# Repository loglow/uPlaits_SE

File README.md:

# µPlaits SE (uPlaits, microPlaits) Eurorack [Rev C]

## 8HP Eurorack module | Macro-oscillator

[µPlaits SE](http://uplaits-se.com) is a voltage-controlled sound source offering direct access to a large palette of easily tweakable raw sonic material generated by models spanning a wide range of synthesis techniques.

This re-engineered Eurorack module miniaturizes and redesigns the original [Mutable Instruments Plaits](https://mutable-instruments.net/modules/plaits/), reducing its size from 12HP to 8HP and reworking its front panel layout.

Fully compatible with upstream Plaits firmware. Includes power cable, mounting hardware, and a one-year warranty. Designed and built with care by [Tall Dog Electronics](http://tall-dog.com) in Western Massachusetts. Licensed [CC BY-SA 4.0](https://creativecommons.org/licenses/by-sa/4.0/) open source hardware.

- **Height:** 3U (128.5 mm)
- **Width:** 8HP (40.3 mm)
- **Depth:** 43 mm (with power)
- **+12V:** 50 mA (average)
- **-12V:** 5 mA (average)

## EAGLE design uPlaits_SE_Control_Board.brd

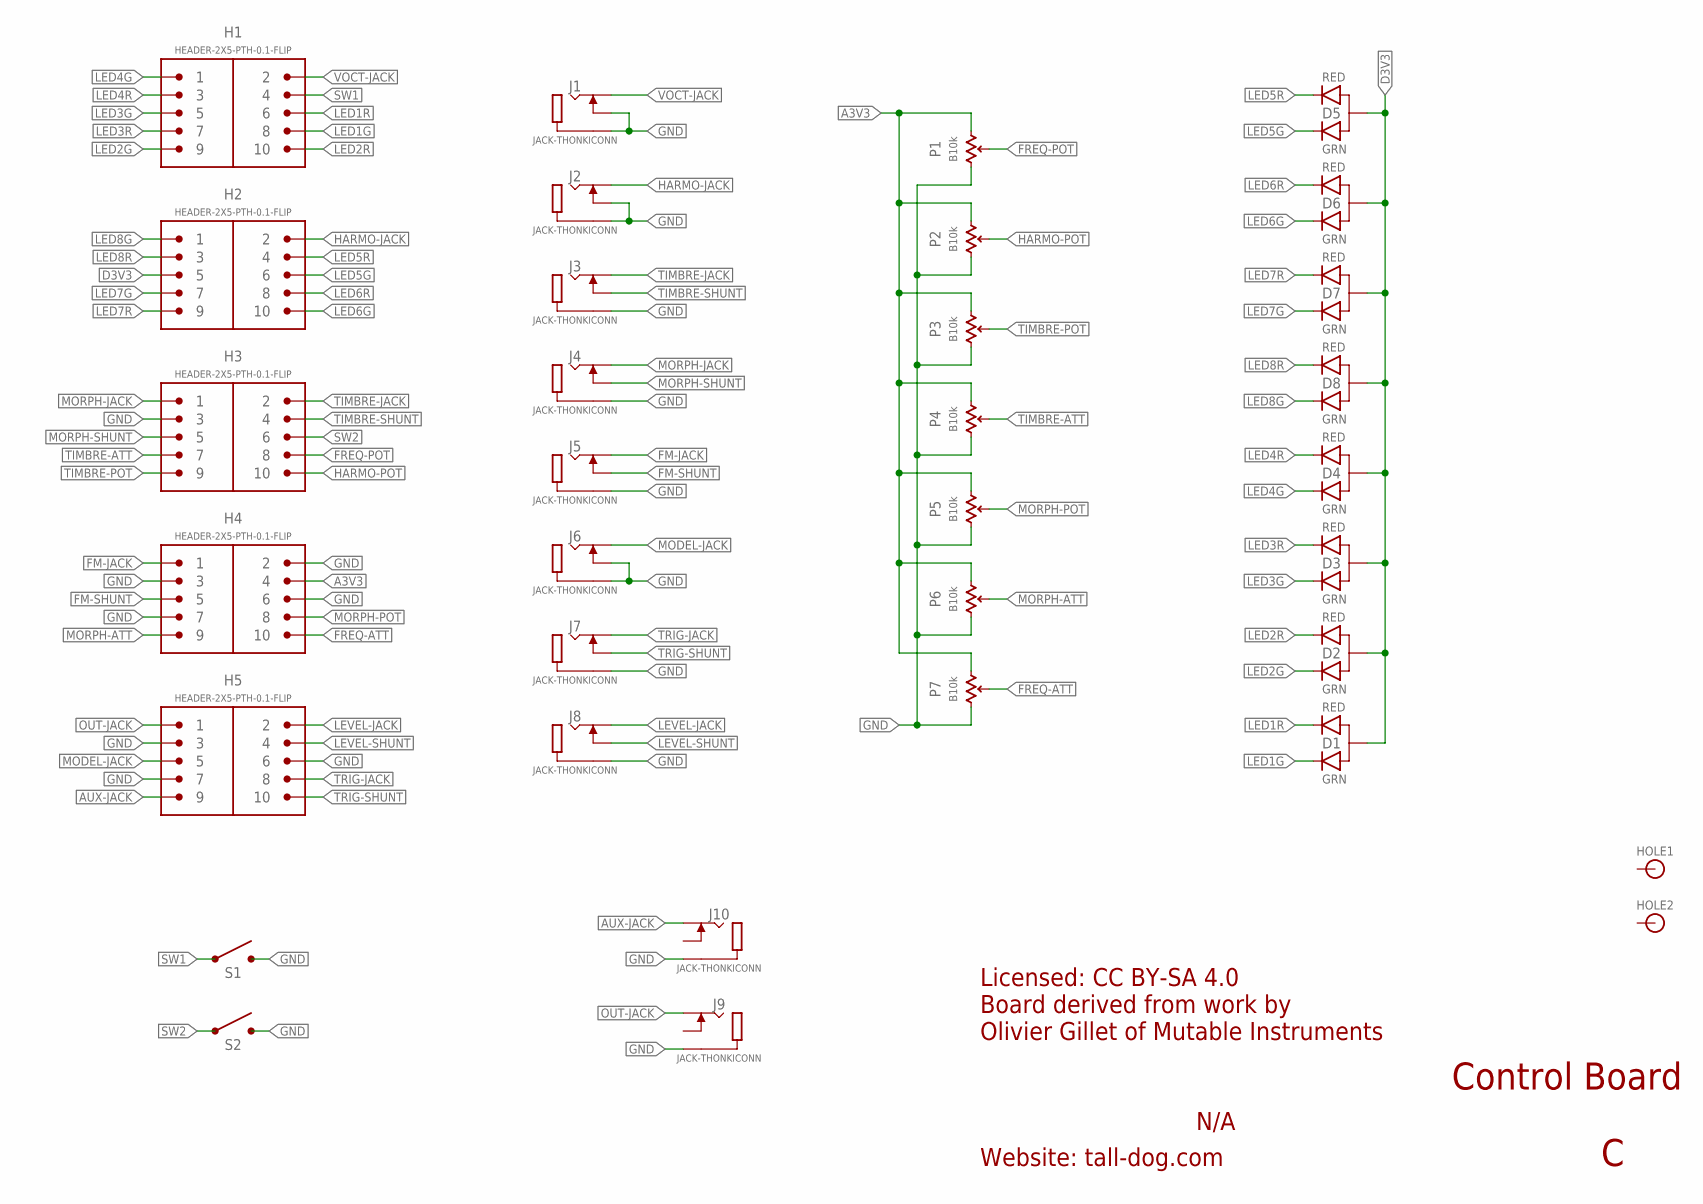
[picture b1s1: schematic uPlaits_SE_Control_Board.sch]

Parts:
D1, D2, D3, D4, D5, D6, D7, D8: LED-DUAL-PTH; LED-T1-3
H1, H2, H3, H4, H5: HEADER-2X5-PTH-0.1-FLIP; PTH-0.1-2X5-FLIP
HOLE1, HOLE2: HOLE; HOLE-M2.5
J1, J2, J3, J4, J5, J6, J7, J8, J9, J10: JACK-THONKICONN; THONKICONN
P1, P2, P3, P4, P5, P6, P7: B10k; POT-SONG-9MM
S1, S2: SPST-PTH; TL1105

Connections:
A3V3: H4.4, P1.P$1 (E), P2.P$1 (E), P3.P$1 (E), P4.P$1 (E), P5.P$1 (E), P6.P$1 (E), P7.P$1 (E)
AUX-JACK: H5.9, J10.P3 (3)
D3V3: D1.2 (A), D2.2 (A), D3.2 (A), D4.2 (A), D5.2 (A), D6.2 (A), D7.2 (A), D8.2 (A), H2.5
FM-JACK: H4.1, J5.P3 (3)
FM-SHUNT: H4.5, J5.P2 (2)
FREQ-ATT: H4.10, P7.P$2 (S)
FREQ-POT: H3.8, P1.P$2 (S)
GND: H3.3, H4.2, H4.3, H4.6, H4.7, H5.3, H5.6, H5.7, J1.P1 (1), J1.P2 (2), J2.P1 (1), J2.P2 (2), J3.P1 (1), J4.P1 (1), J5.P1 (1), J6.P1 (1), J6.P2 (2), J7.P1 (1), J8.P1 (1), J9.P1 (1), J10.P1 (1), P1.P$3 (A), P2.P$3 (A), P3.P$3 (A), P4.P$3 (A), P5.P$3 (A), P6.P$3 (A), P7.P$3 (A), S1.3 (2), S1.4 (2), S2.3 (2), S2.4 (2)
HARMO-JACK: H2.2, J2.P3 (3)
HARMO-POT: H3.10, P2.P$2 (S)
LED1G: D1.3 (GRN), H1.8
LED1R: D1.1 (RED), H1.6
LED2G: D2.3 (GRN), H1.9
LED2R: D2.1 (RED), H1.10
LED3G: D3.3 (GRN), H1.5
LED3R: D3.1 (RED), H1.7
LED4G: D4.3 (GRN), H1.1
LED4R: D4.1 (RED), H1.3
LED5G: D5.3 (GRN), H2.6
LED5R: D5.1 (RED), H2.4
LED6G: D6.3 (GRN), H2.10
LED6R: D6.1 (RED), H2.8
LED7G: D7.3 (GRN), H2.7
LED7R: D7.1 (RED), H2.9
LED8G: D8.3 (GRN), H2.1
LED8R: D8.1 (RED), H2.3
LEVEL-JACK: H5.2, J8.P3 (3)
LEVEL-SHUNT: H5.4, J8.P2 (2)
MODEL-JACK: H5.5, J6.P3 (3)
MORPH-ATT: H4.9, P6.P$2 (S)
MORPH-JACK: H3.1, J4.P3 (3)
MORPH-POT: H4.8, P5.P$2 (S)
MORPH-SHUNT: H3.5, J4.P2 (2)
OUT-JACK: H5.1, J9.P3 (3)
SW1: H1.4, S1.1, S1.2 (1)
SW2: H3.6, S2.1, S2.2 (1)
TIMBRE-ATT: H3.7, P4.P$2 (S)
TIMBRE-JACK: H3.2, J3.P3 (3)
TIMBRE-POT: H3.9, P3.P$2 (S)
TIMBRE-SHUNT: H3.4, J3.P2 (2)
TRIG-JACK: H5.8, J7.P3 (3)
TRIG-SHUNT: H5.10, J7.P2 (2)
VOCT-JACK: H1.2, J1.P3 (3)

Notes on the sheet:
Licensed: CC BY-SA 4.0 Board derived from work by Olivier Gillet of Mutable Instruments
Website: tall-dog.com
N/A
Control Board

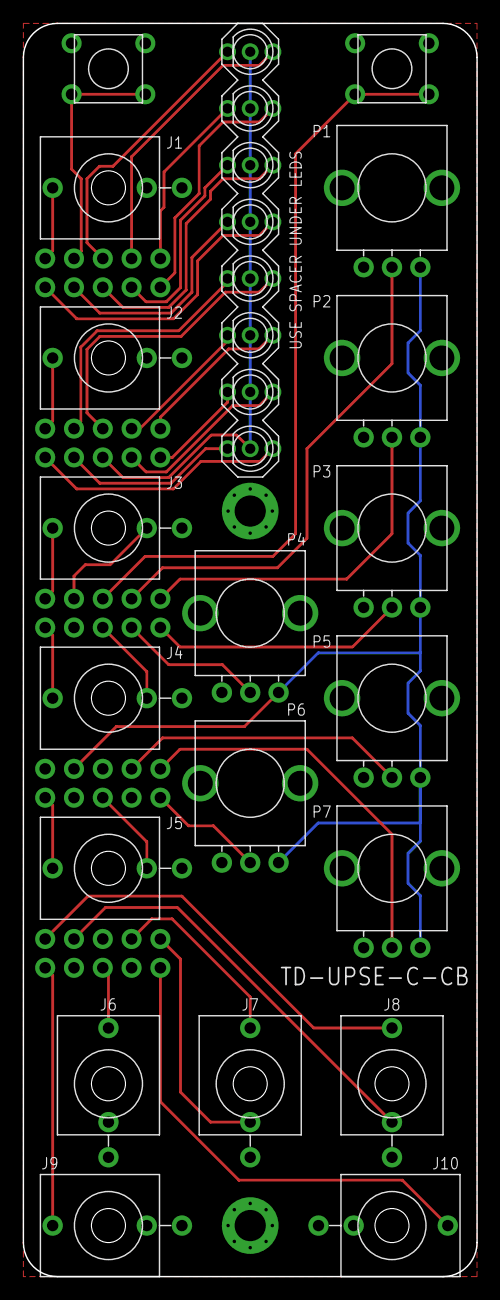
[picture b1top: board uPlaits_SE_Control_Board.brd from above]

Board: 2 copper layers, 40.0 x 110.5 mm, 35 parts (0 on the bottom side), 43 nets.

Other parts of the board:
U$1: LED-SPACER

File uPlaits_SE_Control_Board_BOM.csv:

Ref,Qty,Desc,Mfg,MPN
D1 D2 D3 D4 D5 D6 D7 D8,8,LED GREEN/RED DIFF T-3MM TRI T/H,Lumex Opto/Components Inc.,SSL-LX3059IGW-CA
H1 H2 H3 H4 H5,5,CONN HEADER VERT 10POS 2.54MM,Amphenol ICC (FCI),67997-210HLF
J1 J2 J3 J4 J5 J6 J7 J8 J9 J10,10,3.5MM JACK VERTICAL PCB MOUNT,Wenzhou QingPu,WQP-WQP518MA
P1 P2 P3 P5,4,POT 9MM LINEAR B10K WHITE LINE,Song Huei,"R0904N-B10K,L-25KQ/LWS"
P4 P6 P7,3,POT 9MM LINEAR B10K WHITE LINE CENTER DETENT,Song Huei,"R0904N-B10K,L-25KQ/LWS/CC"
S1 S2,2,SWITCH TACTILE SPST-NO 0.05A 12V,E-Switch,TL1105DF160Q

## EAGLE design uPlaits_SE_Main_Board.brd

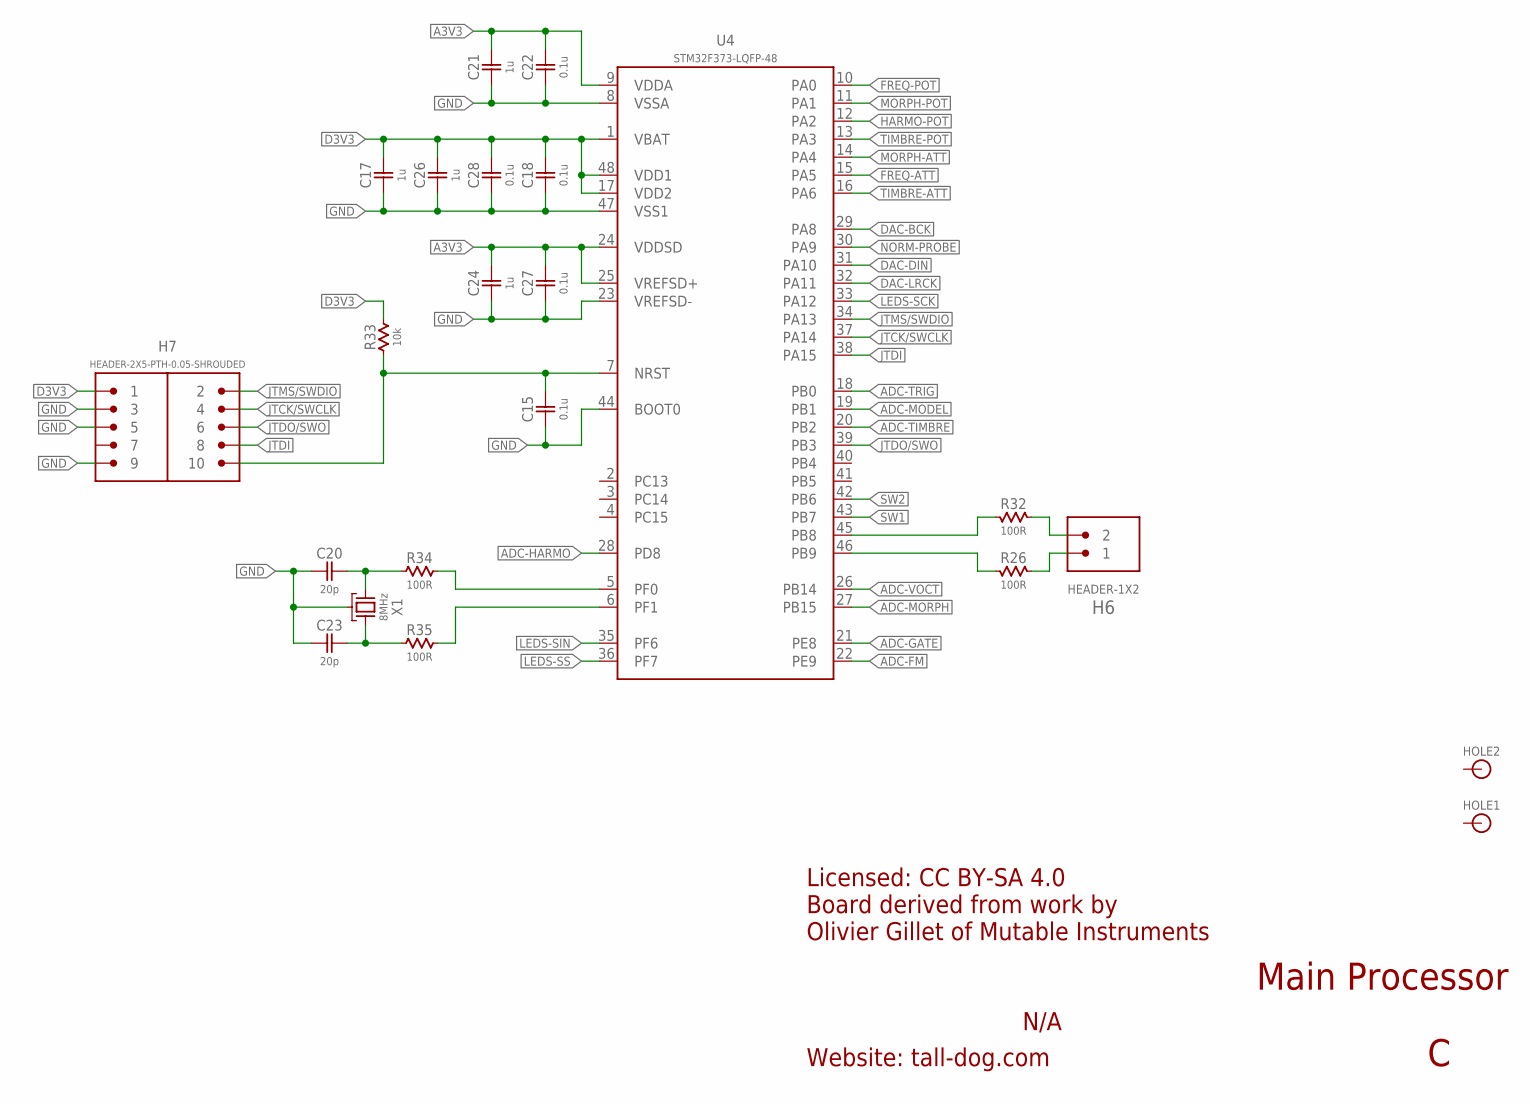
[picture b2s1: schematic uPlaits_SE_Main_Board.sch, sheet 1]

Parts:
C15, C18, C22, C27, C28: 0.1u; 0603-NP
C17, C21, C24, C26: 1u; 0603-NP
C20, C23: 20p; 0603-NP
H6: HEADER-1X2; PTH-0.1-1X2
H7: HEADER-2X5-PTH-0.05-SHROUDED; PTH-0.05-2X5-SHROUDED
HOLE1, HOLE2: HOLE; HOLE-M2.5
R26, R32, R34, R35: 100R; 0603-NP
R33: 10k; 0603-NP
U4: STM32F373-LQFP-48; LQFP-48
X1: 8MHz; CRYSTAL-ABMM2

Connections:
A3V3: C21.2, C22.2, C24.2, C27.2, U4.9 (VDDA), U4.24 (VDDSD), U4.25 (VREFSD+); also elsewhere on the board
ADC-FM: U4.22 (PE9); also elsewhere on the board
ADC-GATE: U4.21 (PE8); also elsewhere on the board
ADC-HARMO: U4.28 (PD8); also elsewhere on the board
ADC-MODEL: U4.19 (PB1); also elsewhere on the board
ADC-MORPH: U4.27 (PB15); also elsewhere on the board
ADC-TIMBRE: U4.20 (PB2); also elsewhere on the board
ADC-TRIG: U4.18 (PB0); also elsewhere on the board
ADC-VOCT: U4.26 (PB14); also elsewhere on the board
D3V3: C17.2, C18.2, C26.2, C28.2, H7.1, R33.2, U4.1 (VBAT), U4.17 (VDD2), U4.48 (VDD1); also elsewhere on the board
DAC-BCK: U4.29 (PA8); also elsewhere on the board
DAC-DIN: U4.31 (PA10); also elsewhere on the board
DAC-LRCK: U4.32 (PA11); also elsewhere on the board
FREQ-ATT: U4.15 (PA5); also elsewhere on the board
FREQ-POT: U4.10 (PA0); also elsewhere on the board
GND: C15.1, C17.1, C18.1, C20.1, C21.1, C22.1, C23.1, C24.1, C26.1, C27.1, C28.1, H7.3, H7.5, H7.9, U4.8 (VSSA), U4.23 (VREFSD-), U4.44 (BOOT0), U4.47 (VSS1), X1.2 (G), X1.4 (G); also elsewhere on the board
HARMO-POT: U4.12 (PA2); also elsewhere on the board
JTCK/SWCLK: H7.4, U4.37 (PA14)
JTDI: H7.8, U4.38 (PA15)
JTDO/SWO: H7.6, U4.39 (PB3)
JTMS/SWDIO: H7.2, U4.34 (PA13)
LEDS-SCK: U4.33 (PA12); also elsewhere on the board
LEDS-SIN: U4.35 (PF6); also elsewhere on the board
LEDS-SS: U4.36 (PF7); also elsewhere on the board
MORPH-ATT: U4.14 (PA4); also elsewhere on the board
MORPH-POT: U4.11 (PA1); also elsewhere on the board
unnamed: C20.2, R34.1, X1.3 (2)
unnamed: C23.2, R35.1, X1.1
unnamed: R34.2, U4.5 (PF0)
unnamed: R35.2, U4.6 (PF1)
NORM-PROBE: U4.30 (PA9); also elsewhere on the board
RESET: C15.2, H7.10, R33.1, U4.7 (NRST)
RX: H6.1, R26.1
RX1: R26.2, U4.46 (PB9)
SW1: U4.43 (PB7); also elsewhere on the board
SW2: U4.42 (PB6); also elsewhere on the board
TIMBRE-ATT: U4.16 (PA6); also elsewhere on the board
TIMBRE-POT: U4.13 (PA3); also elsewhere on the board
TX: H6.2, R32.1
TX1: R32.2, U4.45 (PB8)

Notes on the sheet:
Licensed: CC BY-SA 4.0 Board derived from work by Olivier Gillet of Mutable Instruments
Website: tall-dog.com
N/A
Main Processor

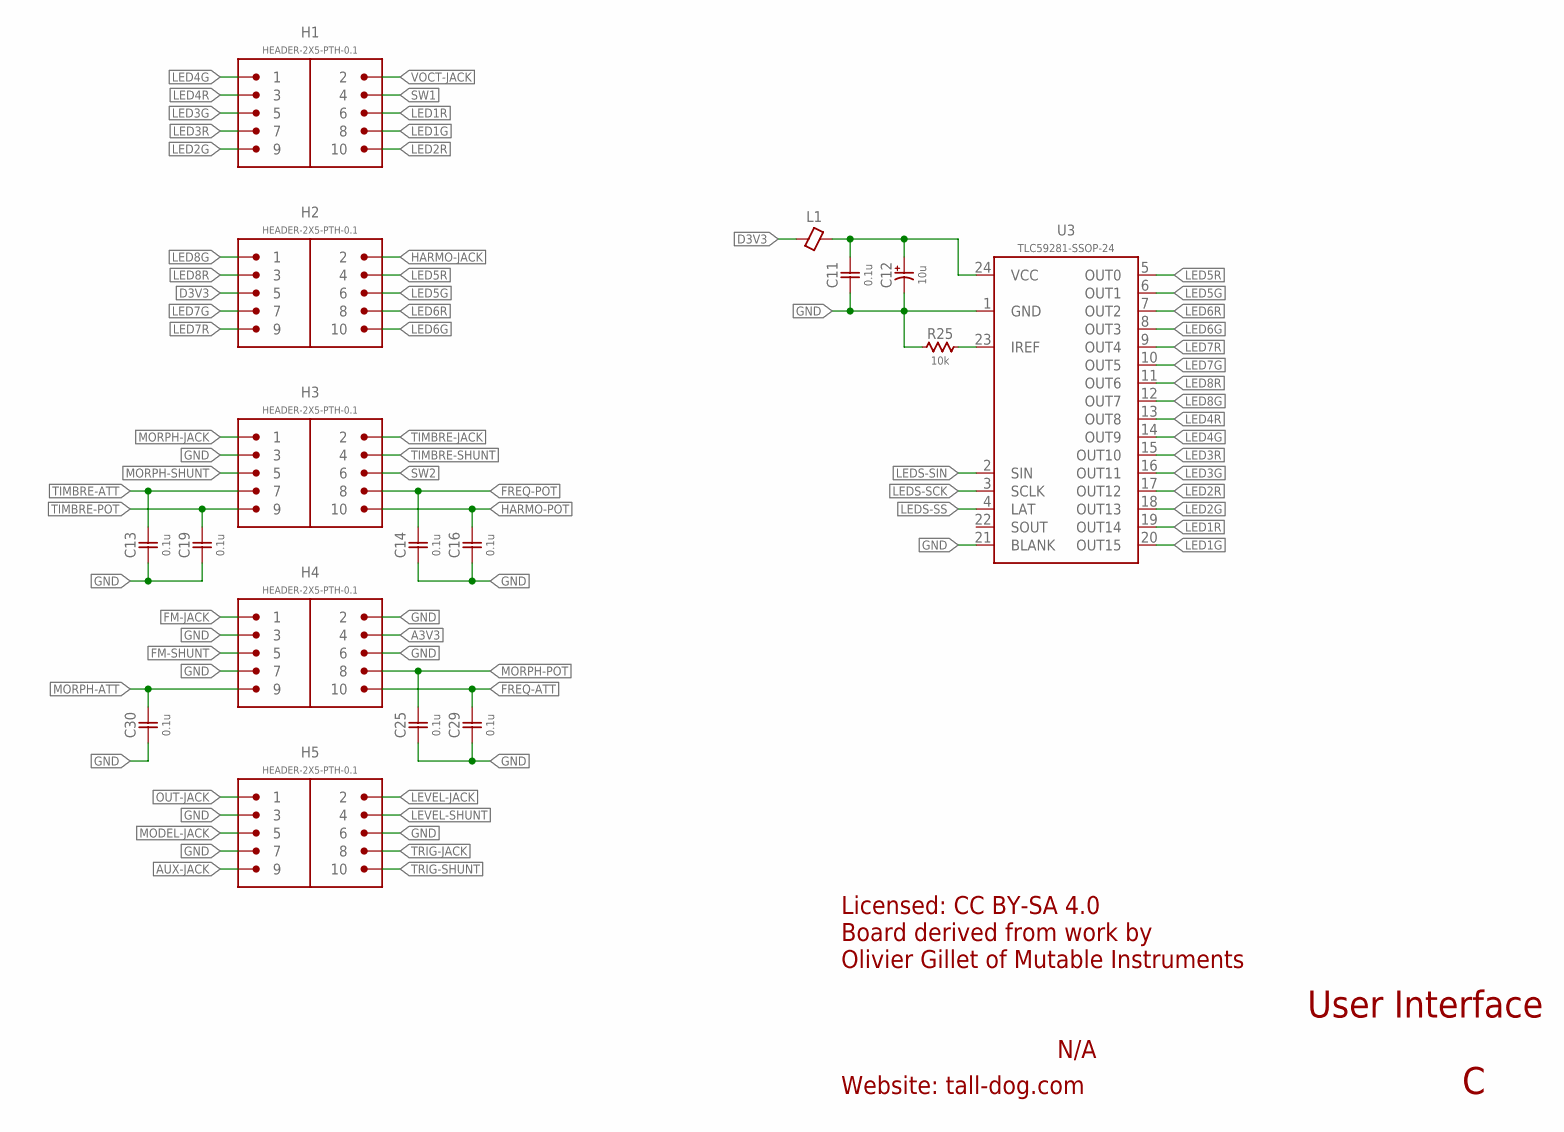
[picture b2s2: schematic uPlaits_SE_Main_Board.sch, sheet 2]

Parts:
C11, C13, C14, C16, C19, C25, C29, C30: 0.1u; 0603-NP
C12: 10u; ELECTRO-SMD-4.3MM
H1, H2, H3, H4, H5: HEADER-2X5-PTH-0.1; PTH-0.1-2X5
L1: FERRITE-BEAD-0603; 0603-NP
R25: 10k; 0603-NP
U3: TLC59281-SSOP-24; SSOP-24

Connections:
A3V3: H4.4; also elsewhere on the board
AUX-JACK: H5.9; also elsewhere on the board
D3V3: H2.5, L1.1; also elsewhere on the board
FM-JACK: H4.1; also elsewhere on the board
FM-SHUNT: H4.5; also elsewhere on the board
FREQ-ATT: C29.2, H4.10; also elsewhere on the board
FREQ-POT: C14.2, H3.8; also elsewhere on the board
GND: C11.1, C12.C (NEG), C13.1, C14.1, C16.1, C19.1, C25.1, C29.1, C30.1, H3.3, H4.2, H4.3, H4.6, H4.7, H5.3, H5.6, H5.7, R25.1, U3.1 (GND), U3.21 (BLANK); also elsewhere on the board
HARMO-JACK: H2.2; also elsewhere on the board
HARMO-POT: C16.2, H3.10; also elsewhere on the board
IREF: R25.2, U3.23 (IREF)
LED1G: H1.8, U3.20 (OUT15)
LED1R: H1.6, U3.19 (OUT14)
LED2G: H1.9, U3.18 (OUT13)
LED2R: H1.10, U3.17 (OUT12)
LED3G: H1.5, U3.16 (OUT11)
LED3R: H1.7, U3.15 (OUT10)
LED4G: H1.1, U3.14 (OUT9)
LED4R: H1.3, U3.13 (OUT8)
LED5G: H2.6, U3.6 (OUT1)
LED5R: H2.4, U3.5 (OUT0)
LED6G: H2.10, U3.8 (OUT3)
LED6R: H2.8, U3.7 (OUT2)
LED7G: H2.7, U3.10 (OUT5)
LED7R: H2.9, U3.9 (OUT4)
LED8G: H2.1, U3.12 (OUT7)
LED8R: H2.3, U3.11 (OUT6)
LEDS-SCK: U3.3 (SCLK); also elsewhere on the board
LEDS-SIN: U3.2 (SIN); also elsewhere on the board
LEDS-SS: U3.4 (LAT); also elsewhere on the board
LEVEL-JACK: H5.2; also elsewhere on the board
LEVEL-SHUNT: H5.4; also elsewhere on the board
MODEL-JACK: H5.5; also elsewhere on the board
MORPH-ATT: C30.2, H4.9; also elsewhere on the board
MORPH-JACK: H3.1; also elsewhere on the board
MORPH-POT: C25.2, H4.8; also elsewhere on the board
MORPH-SHUNT: H3.5; also elsewhere on the board
unnamed: C11.2, C12.A (POS), L1.2, U3.24 (VCC)
OUT-JACK: H5.1; also elsewhere on the board
SW1: H1.4; also elsewhere on the board
SW2: H3.6; also elsewhere on the board
TIMBRE-ATT: C13.2, H3.7; also elsewhere on the board
TIMBRE-JACK: H3.2; also elsewhere on the board
TIMBRE-POT: C19.2, H3.9; also elsewhere on the board
TIMBRE-SHUNT: H3.4; also elsewhere on the board
TRIG-JACK: H5.8; also elsewhere on the board
TRIG-SHUNT: H5.10; also elsewhere on the board
VOCT-JACK: H1.2; also elsewhere on the board

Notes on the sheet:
Licensed: CC BY-SA 4.0 Board derived from work by Olivier Gillet of Mutable Instruments
Website: tall-dog.com
N/A
User Interface

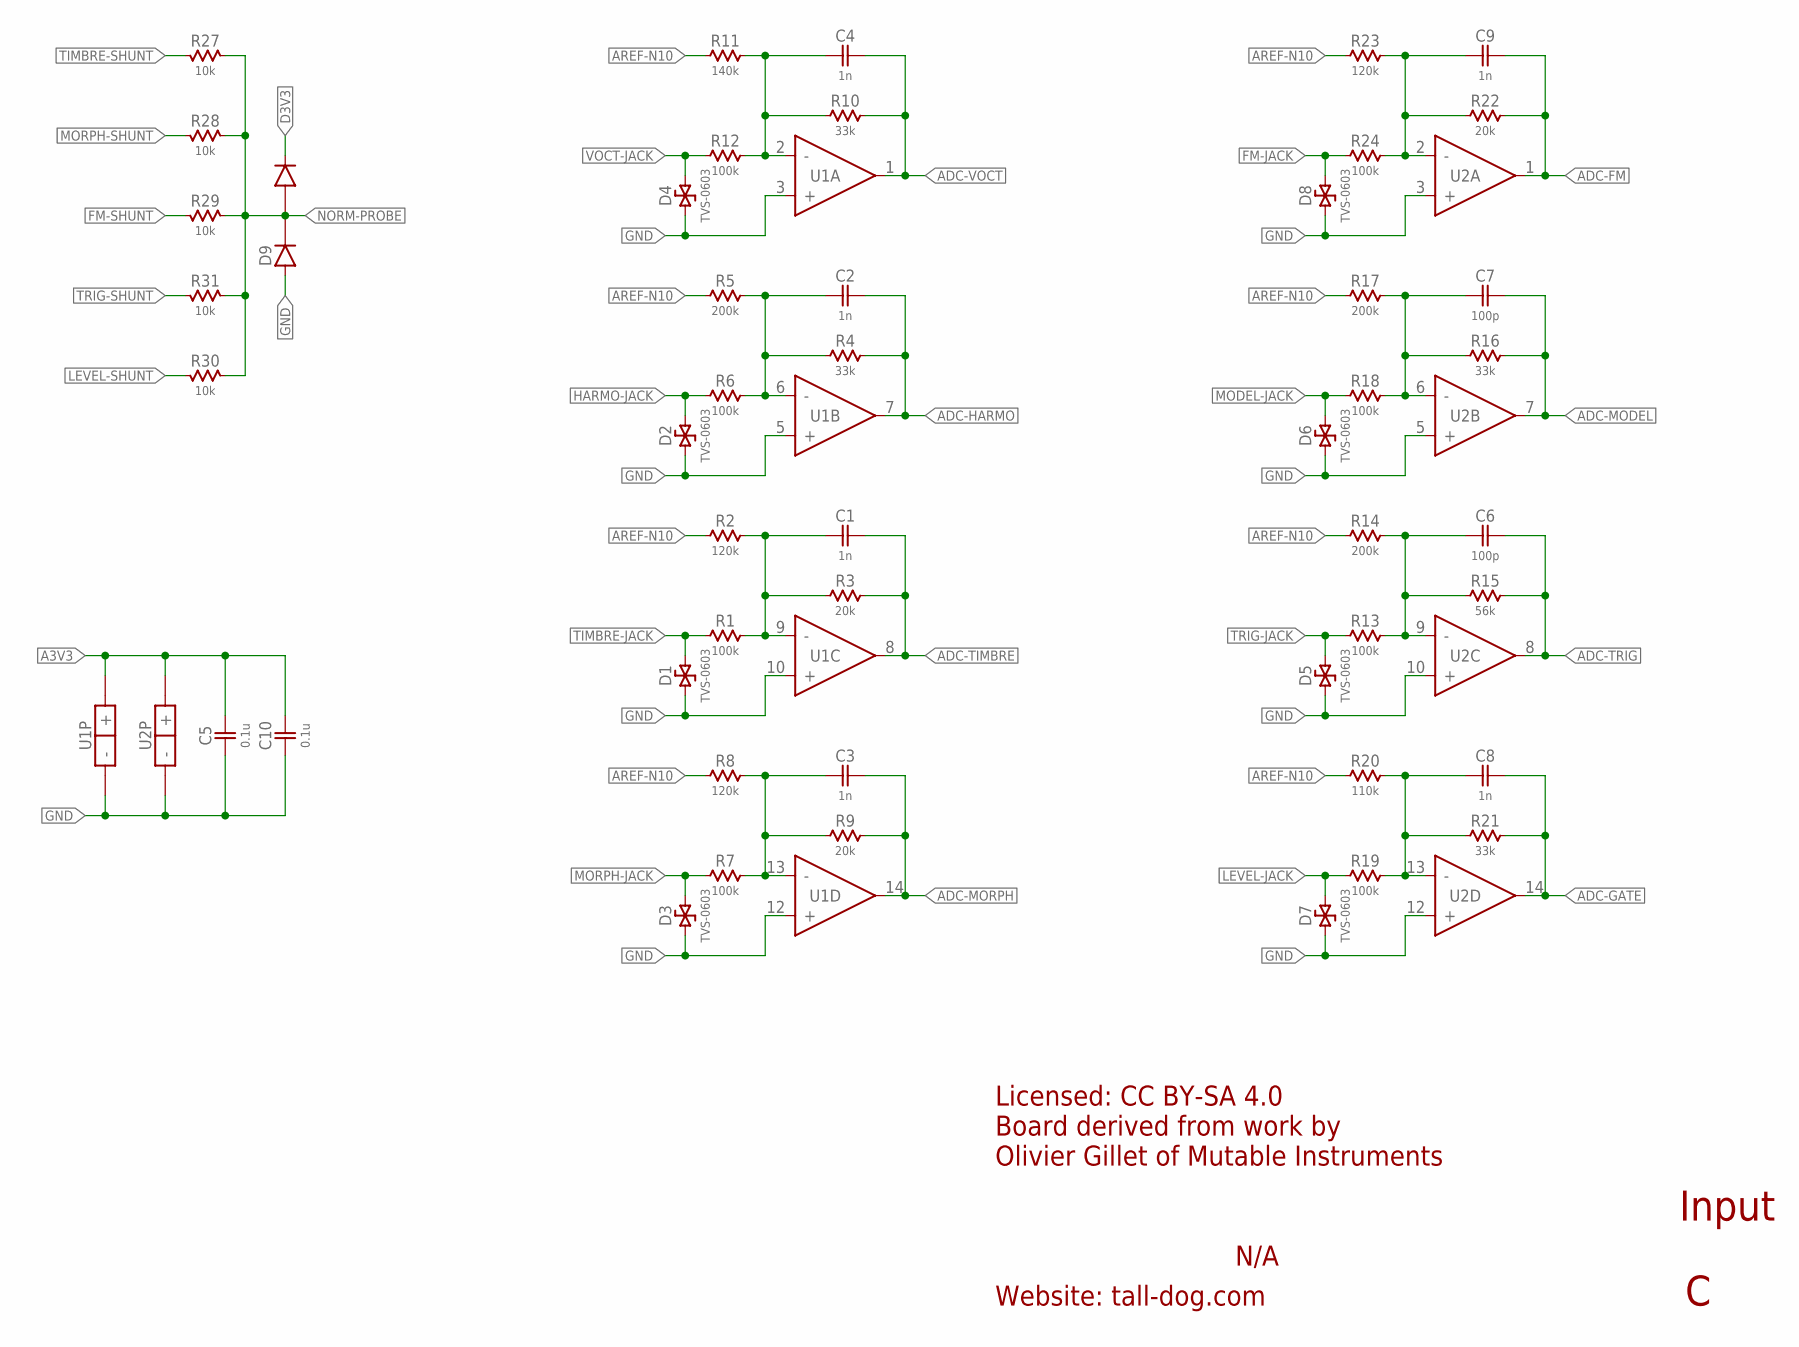
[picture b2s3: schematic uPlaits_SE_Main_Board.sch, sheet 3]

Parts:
C1, C2, C3, C4, C8, C9: 1n; 0603-NP
C5, C10: 0.1u; 0603-NP
C6, C7: 100p; 0603-NP
D1, D2, D3, D4, D5, D6, D7, D8: TVS-0603; 0603-NP
D9: DIODE-DUAL-SOT-23; SOT-23-3
R1, R6, R7, R12, R13, R18, R19, R24: 100k; 0603-NP
R2, R8, R23: 120k; 0603-NP
R3, R9, R22: 20k; 0603-NP
R4, R10, R16, R21: 33k; 0603-NP
R5, R14, R17: 200k; 0603-NP
R11: 140k; 0603-NP
R15: 56k; 0603-NP
R20: 110k; 0603-NP
R27, R28, R29, R30, R31: 10k; 0603-NP
U1, U2: MCP6004-TSSOP-14; TSSOP-14

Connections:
A3V3: C5.2, C10.2, U1.4 (+), U2.4 (+); also elsewhere on the board
ADC-FM: C9.2, R22.2, U2.1 (OUT); also elsewhere on the board
ADC-GATE: C8.2, R21.2, U2.14 (OUT); also elsewhere on the board
ADC-HARMO: C2.2, R4.2, U1.7 (OUT); also elsewhere on the board
ADC-MODEL: C7.2, R16.2, U2.7 (OUT); also elsewhere on the board
ADC-MORPH: C3.2, R9.2, U1.14 (OUT); also elsewhere on the board
ADC-TIMBRE: C1.2, R3.2, U1.8 (OUT); also elsewhere on the board
ADC-TRIG: C6.2, R15.2, U2.8 (OUT); also elsewhere on the board
ADC-VOCT: C4.2, R10.2, U1.1 (OUT); also elsewhere on the board
AREF-N10: R2.1, R5.1, R8.1, R11.1, R14.1, R17.1, R20.1, R23.1; also elsewhere on the board
D3V3: D9.2 (C2); also elsewhere on the board
FM-JACK: D8.2, R24.1; also elsewhere on the board
FM-SHUNT: R29.2; also elsewhere on the board
GND: C5.1, C10.1, D1.1, D2.1, D3.1, D4.1, D5.1, D6.1, D7.1, D8.1, D9.1 (A1), U1.3 (+), U1.5 (+), U1.10 (+), U1.11 (-), U1.12 (+), U2.3 (+), U2.5 (+), U2.10 (+), U2.11 (-), U2.12 (+); also elsewhere on the board
HARMO-JACK: D2.2, R6.1; also elsewhere on the board
LEVEL-JACK: D7.2, R19.1; also elsewhere on the board
LEVEL-SHUNT: R30.2; also elsewhere on the board
MODEL-JACK: D6.2, R18.1; also elsewhere on the board
MORPH-JACK: D3.2, R7.1; also elsewhere on the board
MORPH-SHUNT: R28.2; also elsewhere on the board
unnamed: C4.1, R10.1, R11.2, R12.2, U1.2 (-)
unnamed: C2.1, R4.1, R5.2, R6.2, U1.6 (-)
unnamed: C9.1, R22.1, R23.2, R24.2, U2.2 (-)
unnamed: C1.1, R1.2, R2.2, R3.1, U1.9 (-)
unnamed: C3.1, R7.2, R8.2, R9.1, U1.13 (-)
unnamed: C7.1, R16.1, R17.2, R18.2, U2.6 (-)
unnamed: C6.1, R13.2, R14.2, R15.1, U2.9 (-)
unnamed: C8.1, R19.2, R20.2, R21.1, U2.13 (-)
NORM-PROBE: D9.3 (C1/A2), R27.1, R28.1, R29.1, R30.1, R31.1; also elsewhere on the board
TIMBRE-JACK: D1.2, R1.1; also elsewhere on the board
TIMBRE-SHUNT: R27.2; also elsewhere on the board
TRIG-JACK: D5.2, R13.1; also elsewhere on the board
TRIG-SHUNT: R31.2; also elsewhere on the board
VOCT-JACK: D4.2, R12.1; also elsewhere on the board

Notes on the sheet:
Licensed: CC BY-SA 4.0 Board derived from work by Olivier Gillet of Mutable Instruments
Website: tall-dog.com
N/A
Input

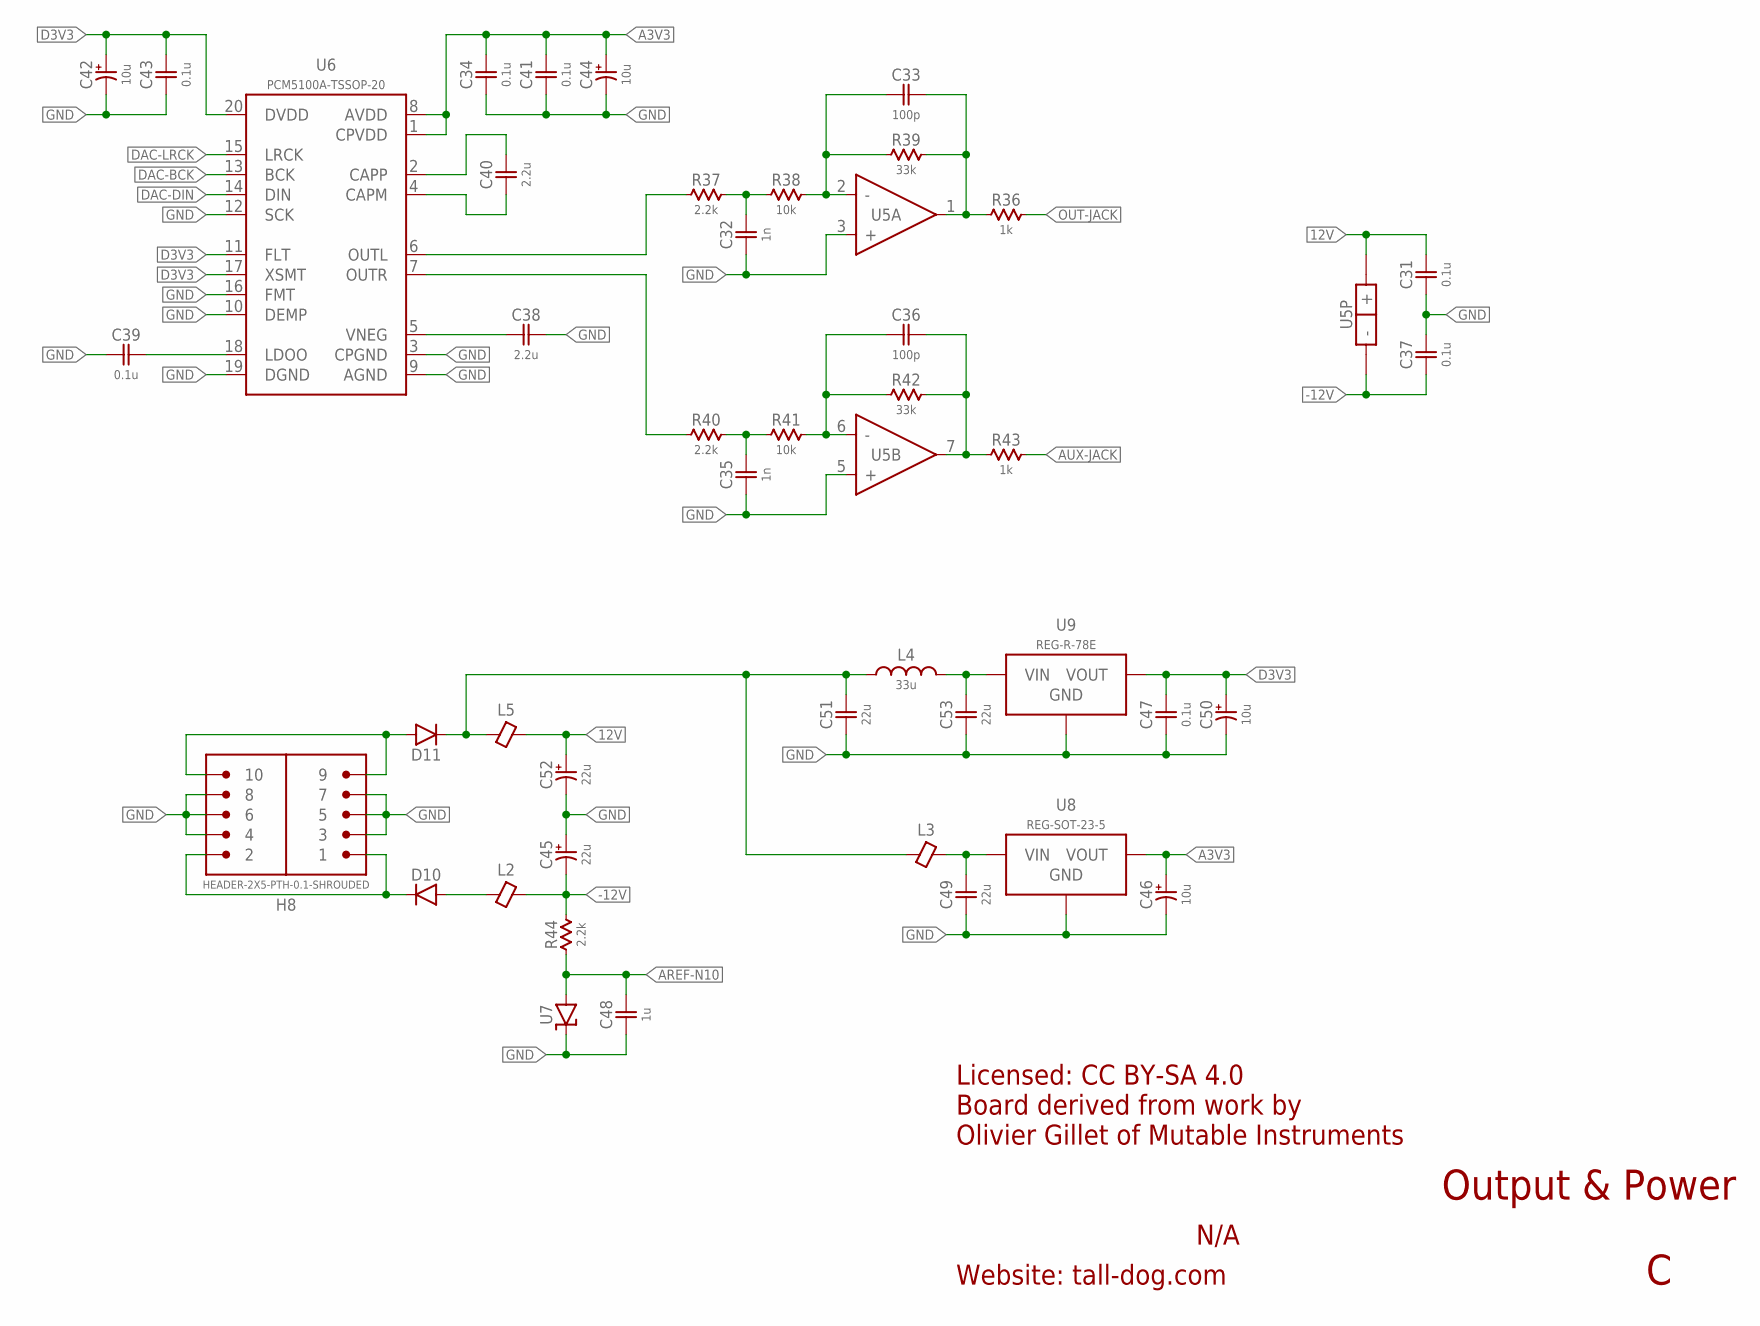
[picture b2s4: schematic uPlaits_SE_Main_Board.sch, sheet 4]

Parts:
C31, C34, C37, C39, C41, C43, C47: 0.1u; 0603-NP
C32, C35: 1n; 0603-NP
C33, C36: 100p; 0603-NP
C38, C40: 2.2u; 0805-NP
C42, C44, C46, C50: 10u; ELECTRO-SMD-4.3MM
C45, C52: 22u; ELECTRO-SMD-6.6MM
C48: 1u; 0603-NP
C49, C51, C53: 22u; 1206-NP
D10, D11: DIODE-SOD123; SOD-123
H8: HEADER-2X5-PTH-0.1-SHROUDED; PTH-0.1-2X5-SHROUDED
L2, L3, L5: FERRITE-BEAD-0603; 0603-NP
L4: 33u; 0805-NP
R36, R43: 1k; 0603-NP
R37, R40, R44: 2.2k; 0603-NP
R38, R41: 10k; 0603-NP
R39, R42: 33k; 0603-NP
U5: TL072-SO-8; SO-8
U6: PCM5100A-TSSOP-20; TSSOP-20
U7: LM4040-SOT-23; SOT-23-3
U8: REG-SOT-23-5; SOT-23-5
U9: REG-R-78E; R-78E

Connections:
12V: C31.2, C52.A (POS), L5.2, U5.8 (+)
12V-IN: D11.A, H8.9, H8.10
-12V: C37.1, C45.C (NEG), L2.2, R44.2, U5.4 (-)
-12V-IN: D10.C, H8.1, H8.2
A3V3: C34.2, C41.2, C44.A (POS), C46.A (POS), U6.1 (CPVDD), U6.8 (AVDD), U8.5 (VOUT); also elsewhere on the board
AREF-N10: C48.2, R44.1, U7.2 (A); also elsewhere on the board
AUX-JACK: R43.2; also elsewhere on the board
D3V3: C42.A (POS), C43.2, C47.2, C50.A (POS), U6.11 (FLT), U6.17 (XSMT), U6.20 (DVDD), U9.3 (VOUT); also elsewhere on the board
DAC-BCK: U6.13 (BCK); also elsewhere on the board
DAC-DIN: U6.14 (DIN); also elsewhere on the board
DAC-LRCK: U6.15 (LRCK); also elsewhere on the board
GND: C31.1, C32.1, C34.1, C35.1, C37.2, C38.2, C39.1, C41.1, C42.C (NEG), C43.1, C44.C (NEG), C45.A (POS), C46.C (NEG), C47.1, C48.1, C49.1, C50.C (NEG), C51.1, C52.C (NEG), C53.1, H8.3, H8.4, H8.5, H8.6, H8.7, H8.8, U5.3 (+), U5.5 (+), U6.3 (CPGND), U6.9 (AGND), U6.10 (DEMP), U6.12 (SCK), U6.16 (FMT), U6.19 (DGND), U7.1 (C), U8.2 (GND), U9.2 (GND); also elsewhere on the board
unnamed: C32.2, R37.2, R38.1
unnamed: C35.2, R40.2, R41.1
unnamed: C33.1, R38.2, R39.1, U5.2 (-)
unnamed: C36.1, R41.2, R42.1, U5.6 (-)
unnamed: C40.2, U6.2 (CAPP)
unnamed: C40.1, U6.4 (CAPM)
unnamed: R37.1, U6.6 (OUTL)
unnamed: R40.1, U6.7 (OUTR)
unnamed: C38.1, U6.5 (VNEG)
unnamed: D10.A, L2.1
unnamed: C51.2, D11.C, L3.1, L4.1, L5.1
unnamed: C36.2, R42.2, R43.1, U5.7 (OUT)
unnamed: C33.2, R36.1, R39.2, U5.1 (OUT)
unnamed: C53.2, L4.2, U9.1 (VIN)
unnamed: C49.2, L3.2, U8.1 (VIN), U8.3 (VIN)
unnamed: C39.2, U6.18 (LDOO)
OUT-JACK: R36.2; also elsewhere on the board

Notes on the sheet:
Licensed: CC BY-SA 4.0 Board derived from work by Olivier Gillet of Mutable Instruments
Website: tall-dog.com
N/A
Output & Power

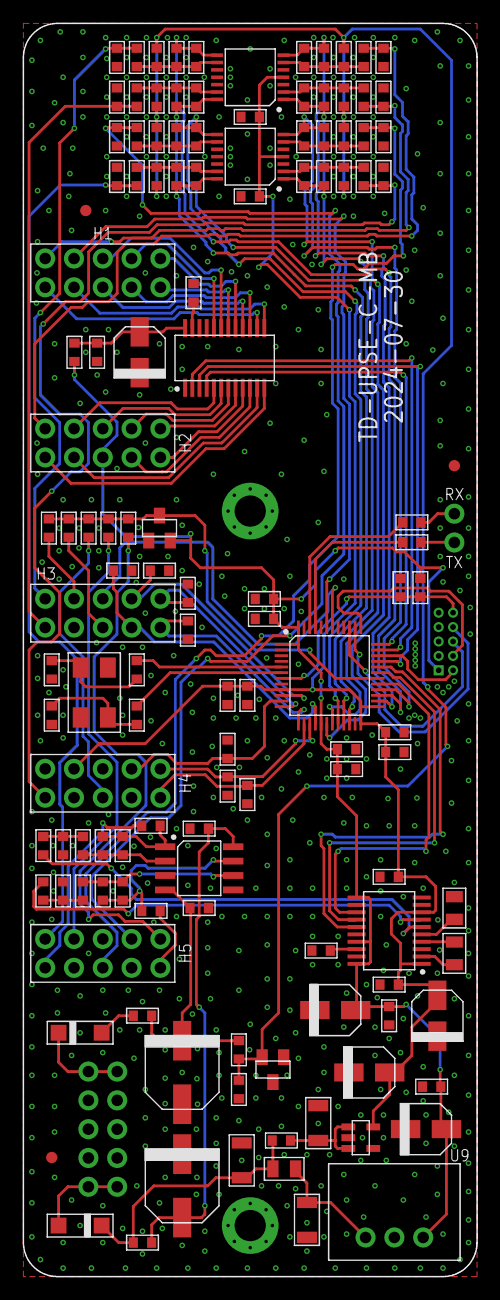
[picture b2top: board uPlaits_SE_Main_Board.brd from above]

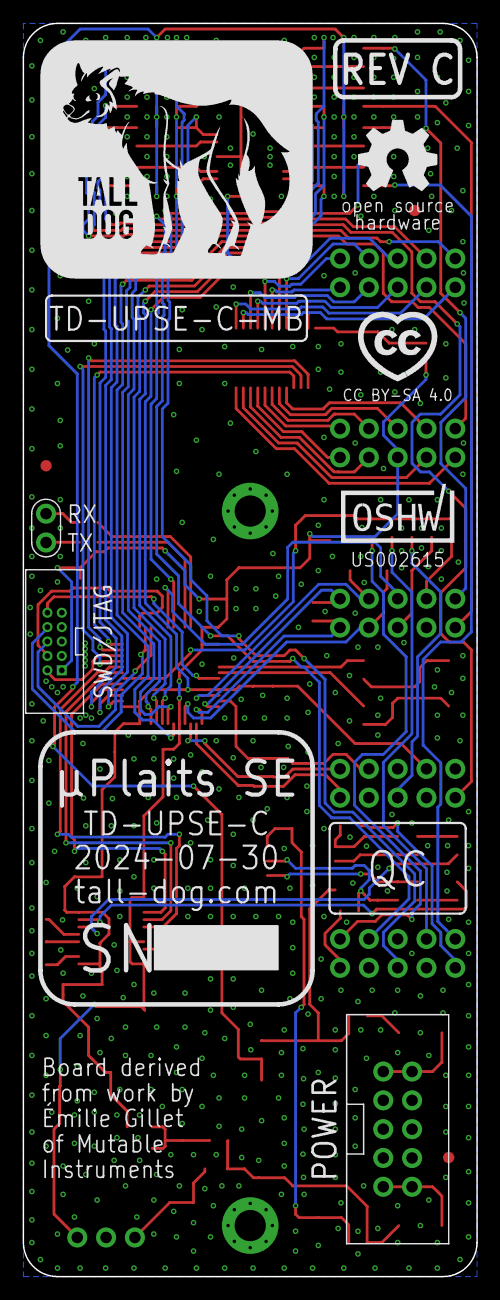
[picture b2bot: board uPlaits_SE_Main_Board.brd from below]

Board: 2 copper layers, 40.0 x 110.5 mm, 144 parts (11 on the bottom side), 102 nets.

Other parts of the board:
U$1: LOGO-TD
U$6, U$7, U$8: FIDUCIAL
U$9: LOGO-CC
U$10: LOGO-OSH
U$11: LOGO-OSHW
U$12: LOGO-PN
U$13: LOGO-QC
U$14: LOGO-REV
U$15: LOGO-SN

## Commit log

2021-03-23 Revision B
2024-07-07 updates and cleanup for Rev C production run
2024-07-07 changed Assembly Template to green for consistency
2024-07-13 small BOM correction
2024-07-20 updated jack part number, added control board XYR, updated main board XYR slightly
2024-08-08 revision C updates continued
